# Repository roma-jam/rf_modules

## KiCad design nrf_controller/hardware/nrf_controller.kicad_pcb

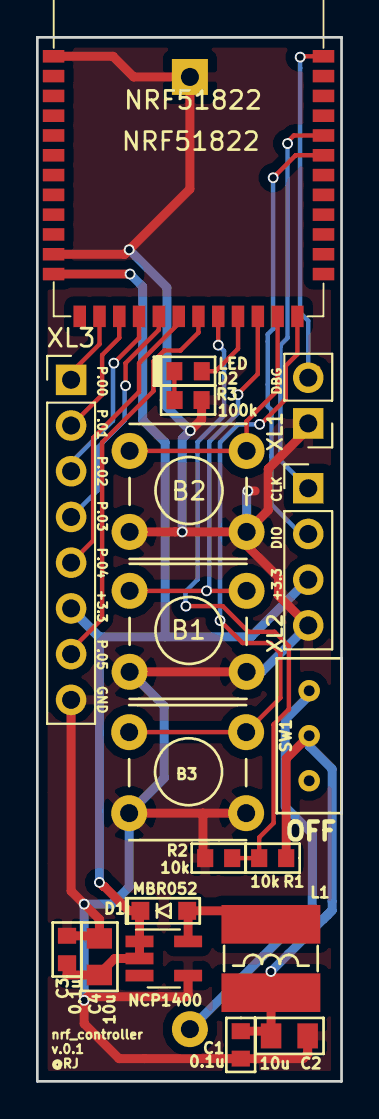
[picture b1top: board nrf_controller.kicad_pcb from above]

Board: 2 copper layers, 16.9 x 58.0 mm, 20 parts (1 on the bottom side), 20 nets.

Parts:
B1, B2, B3: BUTTON; PUSH_THRHOLE_3-1825910-5
C1, C3: 0.1u; CAP_0603
C2, C4: 10u; CAP_0805
D1: MBR052; SOD323
D2: LED; LED_0603
L1: 22uH; CD_type_6.0X5.5
NCP1400: NCP1400; SOT-23-5_HandSoldering
R1, R2: 10k; RES_0603
R3: 100k; RES_0603
SW1: SWITCH; SW_SS-1P2T
U1: NRF51822; YJ-14015-NRF51822_Module
XL1: CONN_2; Socket_Strip_Straight_1x02_Pitch2.54mm
XL2: CONN_4; Socket_Strip_Straight_1x04_Pitch2.54mm
XL3: CONN_8; Socket_Strip_Straight_1x08_Pitch2.54mm
XL4: CONN_2; 1xAA_BAT_HOLDER_PCB

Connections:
+3.3V: C3.1, C4.1, D1.C, NCP1400.1, NCP1400.2, U1.12, XL2.3, XL3.6
+BATT: C1.1, C2.1, L1.2, R1.1, SW1.2
/BAT: SW1.1, XL4.2
/BAT_MEASURE: R1.2, R2.1, U1.20
/BUTTON1: B1.1, U1.22
/BUTTON2: B2.1, U1.23
/BUTTON3: B3.1, U1.24
/DBG_TX: U1.36, XL1.2
/LCD_BCKLT: U1.19, XL3.7
/LCD_CE: U1.15, XL3.2
/LCD_CLK: U1.18, XL3.5
/LCD_DC: U1.16, XL3.3
/LCD_DIN: U1.17, XL3.4
/LCD_RESET: U1.14, XL3.1
/LED: D2.A, U1.21
/PWR_IN: D1.A, L1.1, NCP1400.5
/SWCLK: U1.32, XL2.1
/SWDIO: U1.31, XL2.2
GND: B1.2, B2.2, B3.2, C1.2, C2.2, C3.2, C4.2, NCP1400.4, R2.2, R3.2, U1.1, U1.11, XL1.1, XL2.4, XL3.8, XL4.1
unnamed: D2.C, R3.1

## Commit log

2019-06-26 + Add project files.
2019-06-27 + Complete PCB design.
